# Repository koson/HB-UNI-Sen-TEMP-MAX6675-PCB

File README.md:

# HB-UNI-Sen-TEMP-MAX6675-PCB

Platine zu https://github.com/jp112sdl/HB-UNI-Sen-TEMP-MAX6675 

Status ist  **WIP**

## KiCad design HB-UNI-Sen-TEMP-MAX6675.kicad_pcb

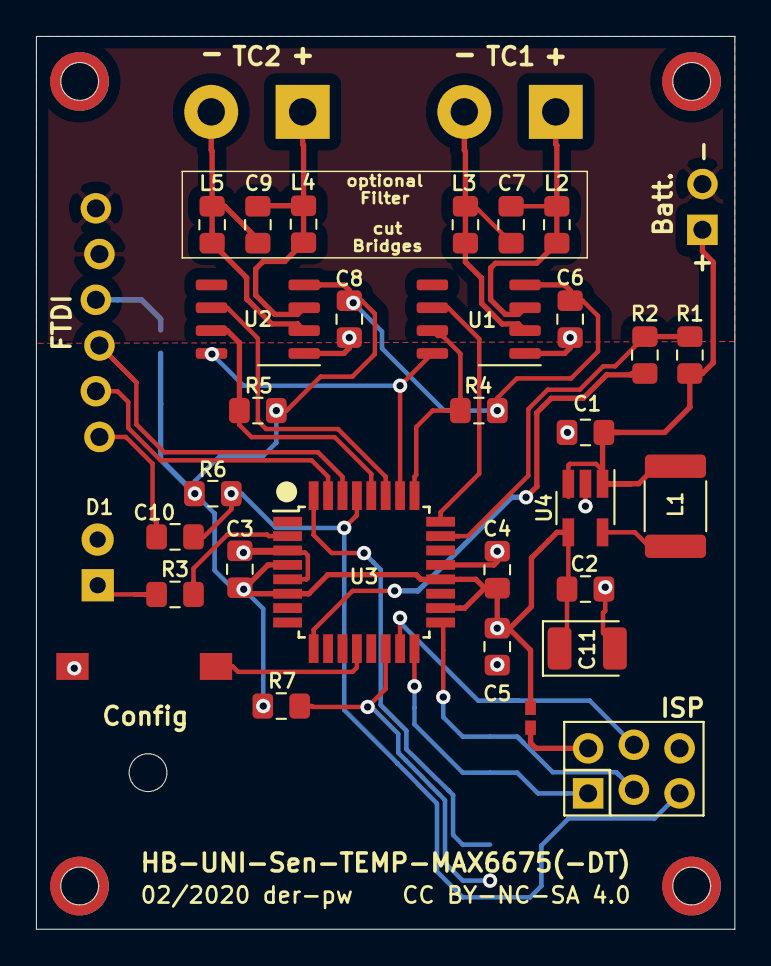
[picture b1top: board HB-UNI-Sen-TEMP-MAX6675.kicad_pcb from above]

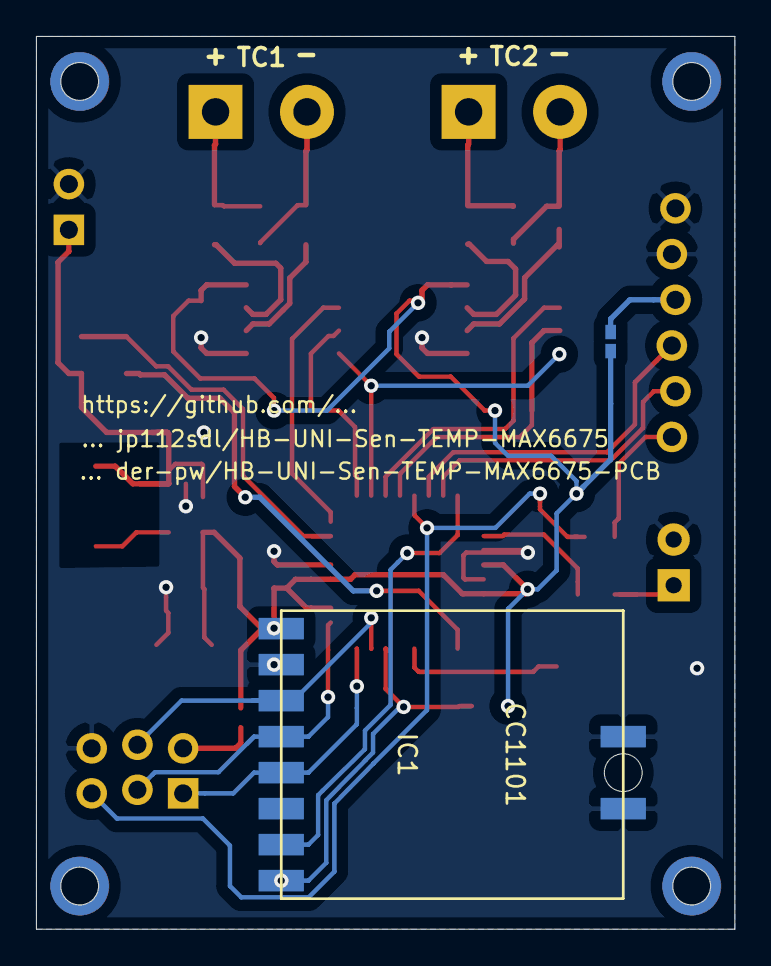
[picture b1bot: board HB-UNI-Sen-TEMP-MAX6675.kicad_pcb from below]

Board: 2 copper layers, 38.8 x 49.6 mm, 41 parts (2 on the bottom side), 33 nets.

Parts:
C1, C2, C5: 10µ; C_0805_2012Metric_Pad1.15x1.40mm_HandSolder
C3, C4, C6, C8, C10: 100n; C_0805_2012Metric_Pad1.15x1.40mm_HandSolder
C7, C9: 10n; C_0805_2012Metric_Pad1.15x1.40mm_HandSolder
C11: 22µ; CP_EIA-3528-21_Kemet-B
D1: LED; LED_D3.0mm
IC1: CC1101; CC1101_Module
J1: TC1; TerminalBlock_bornier-2_P5.08mm
J2: TC2; TerminalBlock_bornier-2_P5.08mm
J3: FTDI; PinHeader_1x06_P2.54mm_Vertical
J4: Conn_01x02_Female; PinHeader_1x02_P2.54mm_Vertical
J5: AVR-ISP-6; PinHeader_2x03_P2.54mm_Vertical
JP1, JP2, JP3, JP4: Jumper_NC_Small; mysmall_Jumper2
JP5, JP6: VCC-Jumper; SolderJumper-2_P1.3mm_Open_RoundedPad1.0x1.5mm
L1: L; L_1812_4532Metric_Pad1.30x3.40mm_HandSolder
L2, L3, L4, L5: L; L_0805_2012Metric_Pad1.15x1.40mm_HandSolder
R1: 470k; R_0805_2012Metric_Pad1.15x1.40mm_HandSolder
R2: 100k; R_0805_2012Metric_Pad1.15x1.40mm_HandSolder
R3: R330; R_0805_2012Metric_Pad1.15x1.40mm_HandSolder
R4, R5, R6, R7: 10k; R_0805_2012Metric_Pad1.15x1.40mm_HandSolder
SW1: Config; SW_SPST_CK_RS282G05A3
U1, U2: MAX6675; SO-8_3.9x4.9mm_P1.27mm
U3: ATmega328P-AU; TQFP-32_7x7mm_P0.8mm
U4: MAX1724; SOT-23-5_HandSoldering

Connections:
/BATT_EN_PIN: R2.1, U3.9
/BATT_MEAS_PIN: R1.1, R2.2, U3.23
/MAX6675_1_CS: R4.1, U1.7, U3.25
/MAX6675_1_SO: U1.6, U3.24
/MAX6675_2_CS: R5.1, U2.7, U3.28
/MAX6675_2_SO: U2.6, U3.27
/MAX6675_SCK: U1.8, U2.8, U3.26
/MISO: IC1.5, J5.1, U3.16
/MOSI: IC1.3, J5.4, U3.15
/RESET: C10.2, J5.5, R6.1, U3.29
/RX: J3.4, U3.30
/SCLK: IC1.4, J5.3, U3.17
/TC_1+: L2.2, U1.3
/TC_1-: L3.2, U1.2
/TC_2+: L4.2, U2.3
/TC_2-: L5.2, U2.2
/TX: J3.5, U3.31
/VIN: C1.1, J4.2, L1.1, R1.2, U4.1, U4.3
GND: C1.2, C2.2, C3.2, C4.2, C5.2, C6.1, C8.1, C11.2, D1.1, IC1.2, IC1.10, IC1.11, J3.1, J3.2, J4.1, J5.6, SW1.2, U1.1, U2.1, U3.3, U3.5, U3.21, U4.2
unnamed: C7.1, J1.1, L2.1
unnamed: C7.2, J1.2, L3.1
unnamed: C9.1, J2.1, L4.1
unnamed: C9.2, J2.2, L5.1
unnamed: C10.1, J3.6
unnamed: D1.2, R3.1
unnamed: IC1.7, U3.32
unnamed: IC1.8, R7.1, U3.14
unnamed: J3.3, JP6.2
unnamed: J5.2, JP5.2
unnamed: L1.2, U4.5
unnamed: R3.2, U3.2
unnamed: SW1.1, U3.12
VCC: C2.1, C3.1, C4.1, C5.1, C6.2, C8.2, C11.1, IC1.1, JP5.1, JP6.1, R4.2, R5.2, R6.2, R7.2, U1.4, U2.4, U3.4, U3.6, U3.18, U3.20, U4.4

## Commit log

2020-02-09 Rename Readme.md to README.md
2020-02-21 update
    forget a damn via

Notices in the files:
HB-UNI-Sen-TEMP-MAX6675.kicad_pcb:
02/2020 der-pw CC BY-NC-SA 4.0
